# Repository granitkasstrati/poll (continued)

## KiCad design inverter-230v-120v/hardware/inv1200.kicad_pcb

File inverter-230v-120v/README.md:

# inv1200: 230 VAC → 120 VAC, 1200 W pure-sine converter

Non-isolated AC-DC-AC converter: inrush limiting, a UCC28180 CCM boost PFC to 400 V, a SiC full-bridge
inverter (unipolar SPWM, 40 kHz carrier, 80 kHz ripple), an LC filter, and an ESP32 controller.

| Path | What |
|---|---|
| `docs/DESIGN.md` | spec, calculations, protection, **what to verify**, bring-up procedure |
| `docs/PCB.md` | layout, clearance rules, regeneration steps |
| `hardware/inv1200.kicad_pro` | KiCad 7 project (schematic + PCB) |
| `hardware/fab/` | Gerbers + drill (zip), BOM CSV, pick-and-place, PDFs, renders |
| `hardware/gen/` | Python generators: `design.py` is the single source of truth for parts and nets |
| `firmware/inv1200/` | ESP-IDF ≥ 5.2 controller skeleton (**untested**) |

**Danger:** the whole board, including the ESP32 GND, is at mains potential; the 400 V bus holds ~94 J; and the 120 V
output is not isolated from the mains. Read `docs/DESIGN.md` §0/§7 before powering anything.

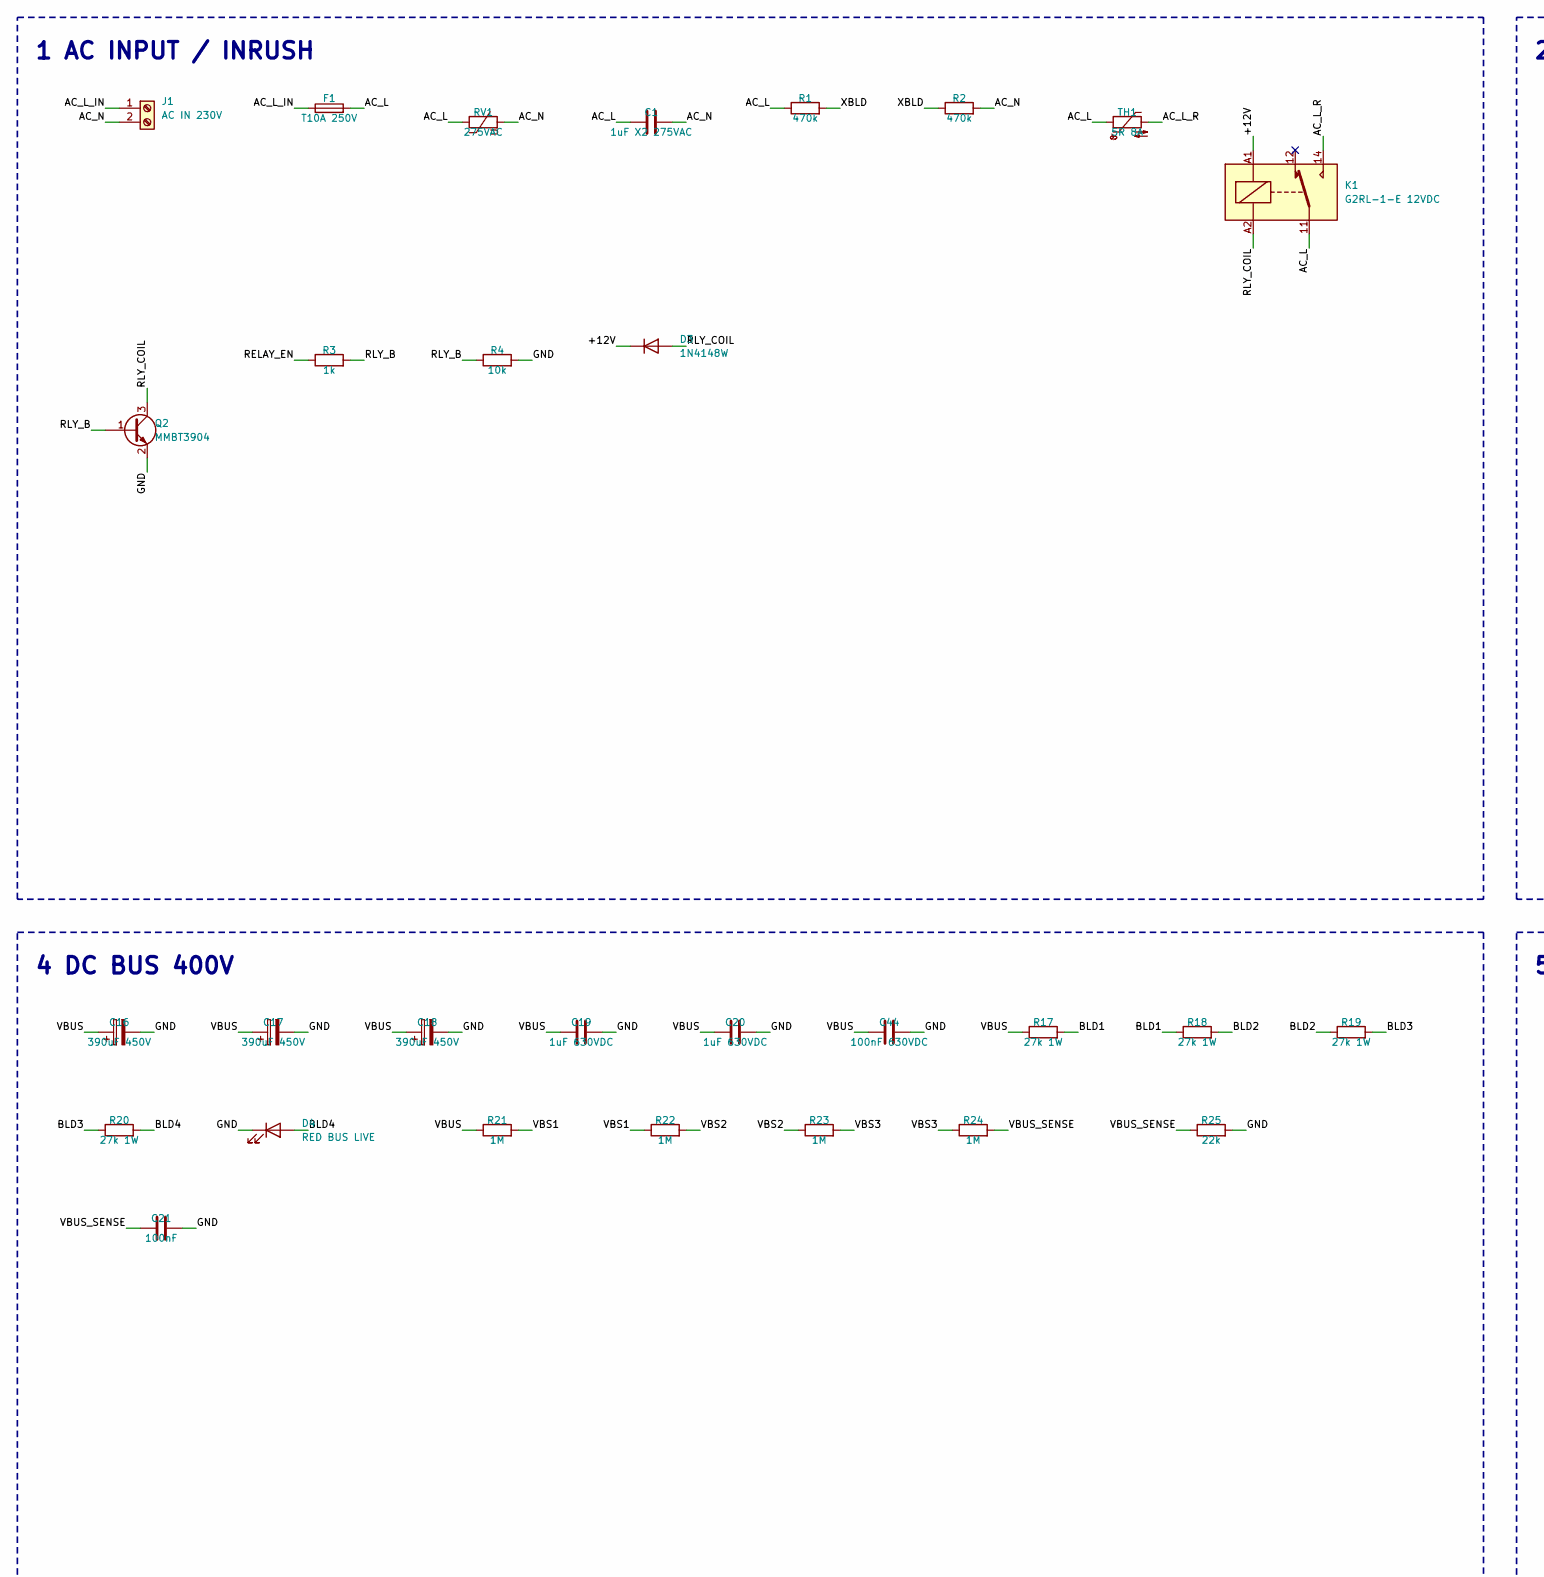
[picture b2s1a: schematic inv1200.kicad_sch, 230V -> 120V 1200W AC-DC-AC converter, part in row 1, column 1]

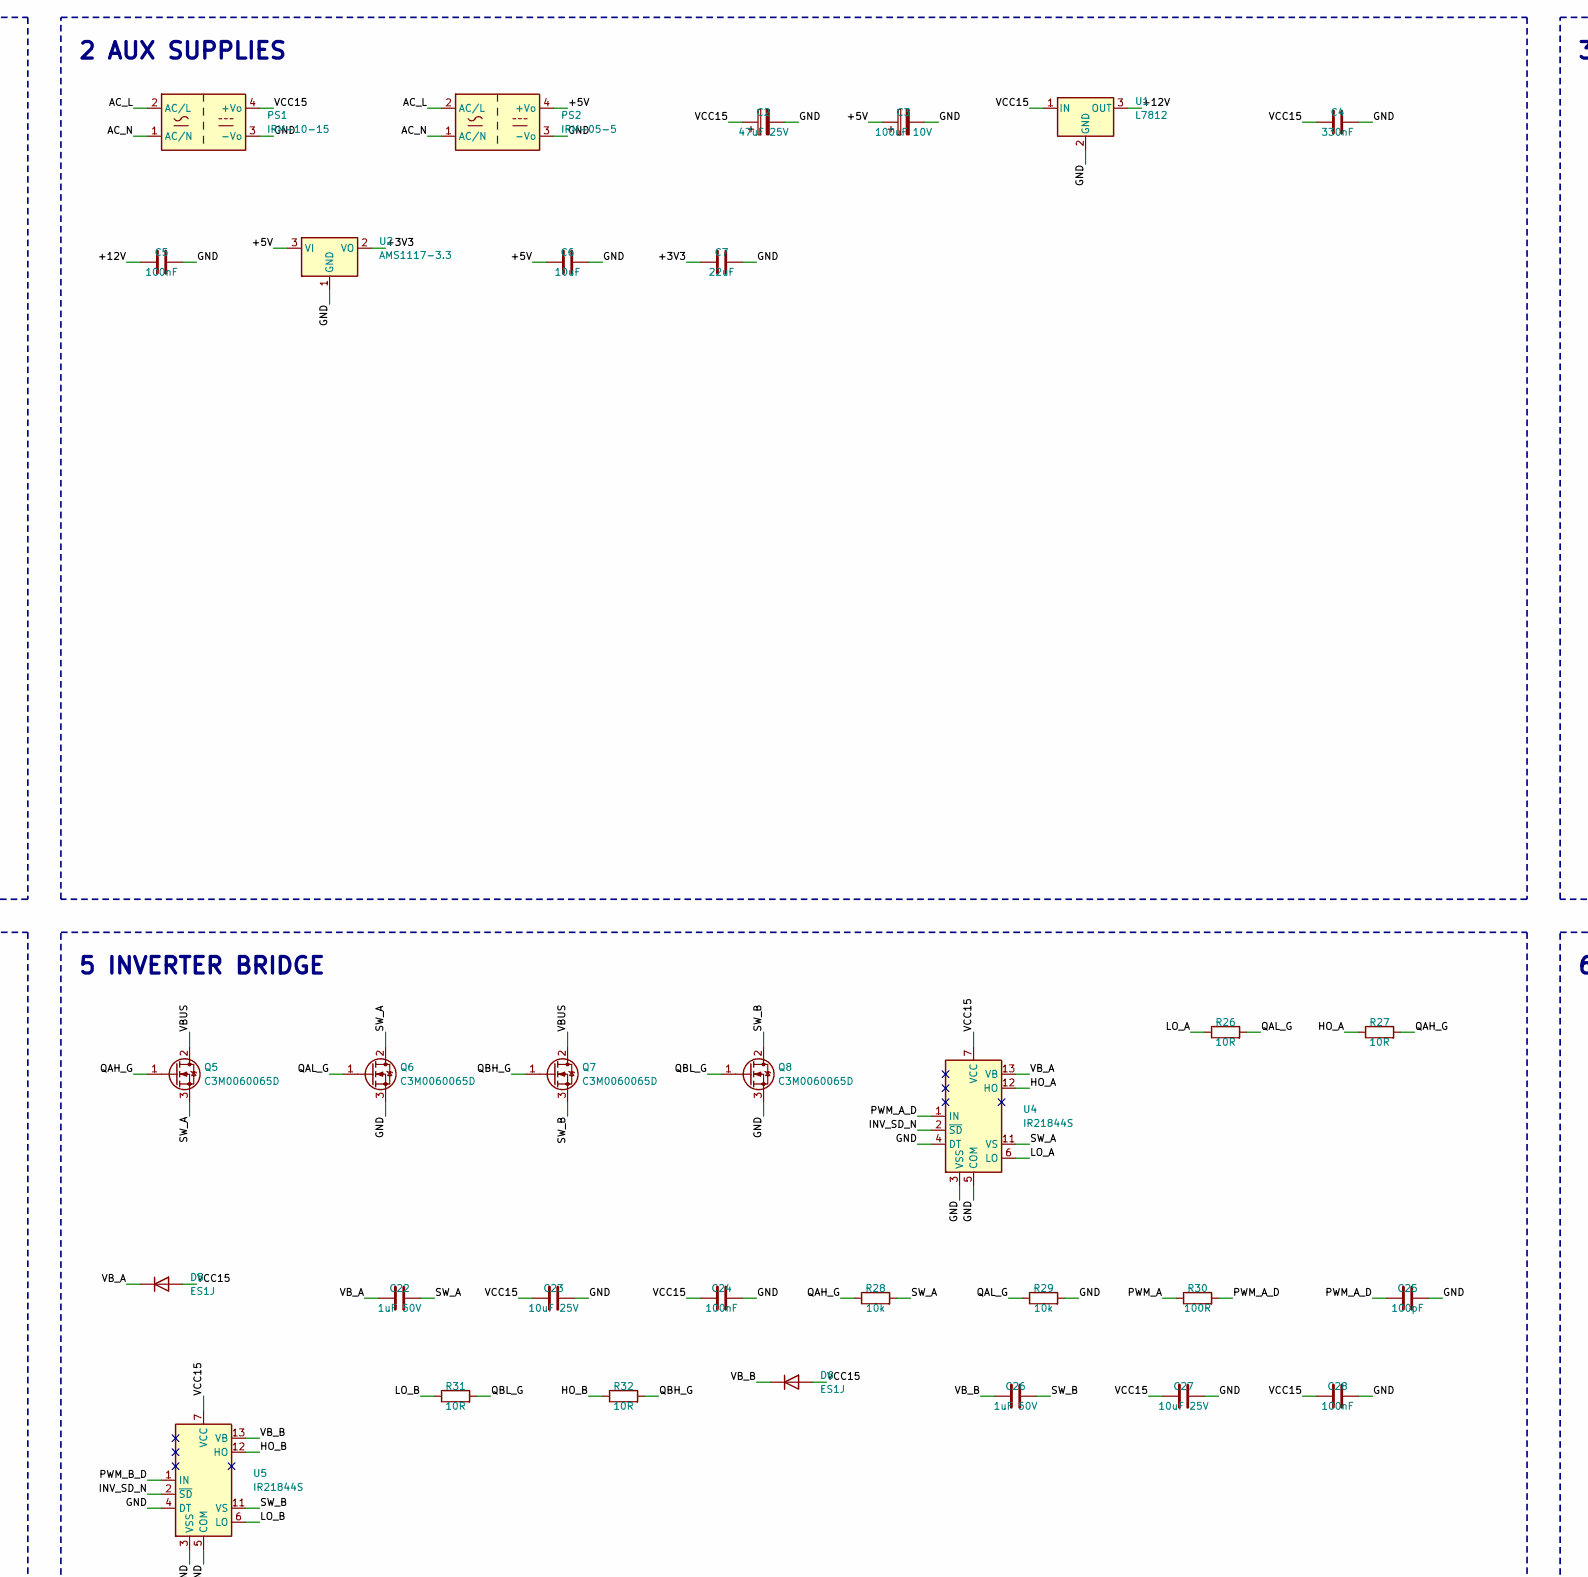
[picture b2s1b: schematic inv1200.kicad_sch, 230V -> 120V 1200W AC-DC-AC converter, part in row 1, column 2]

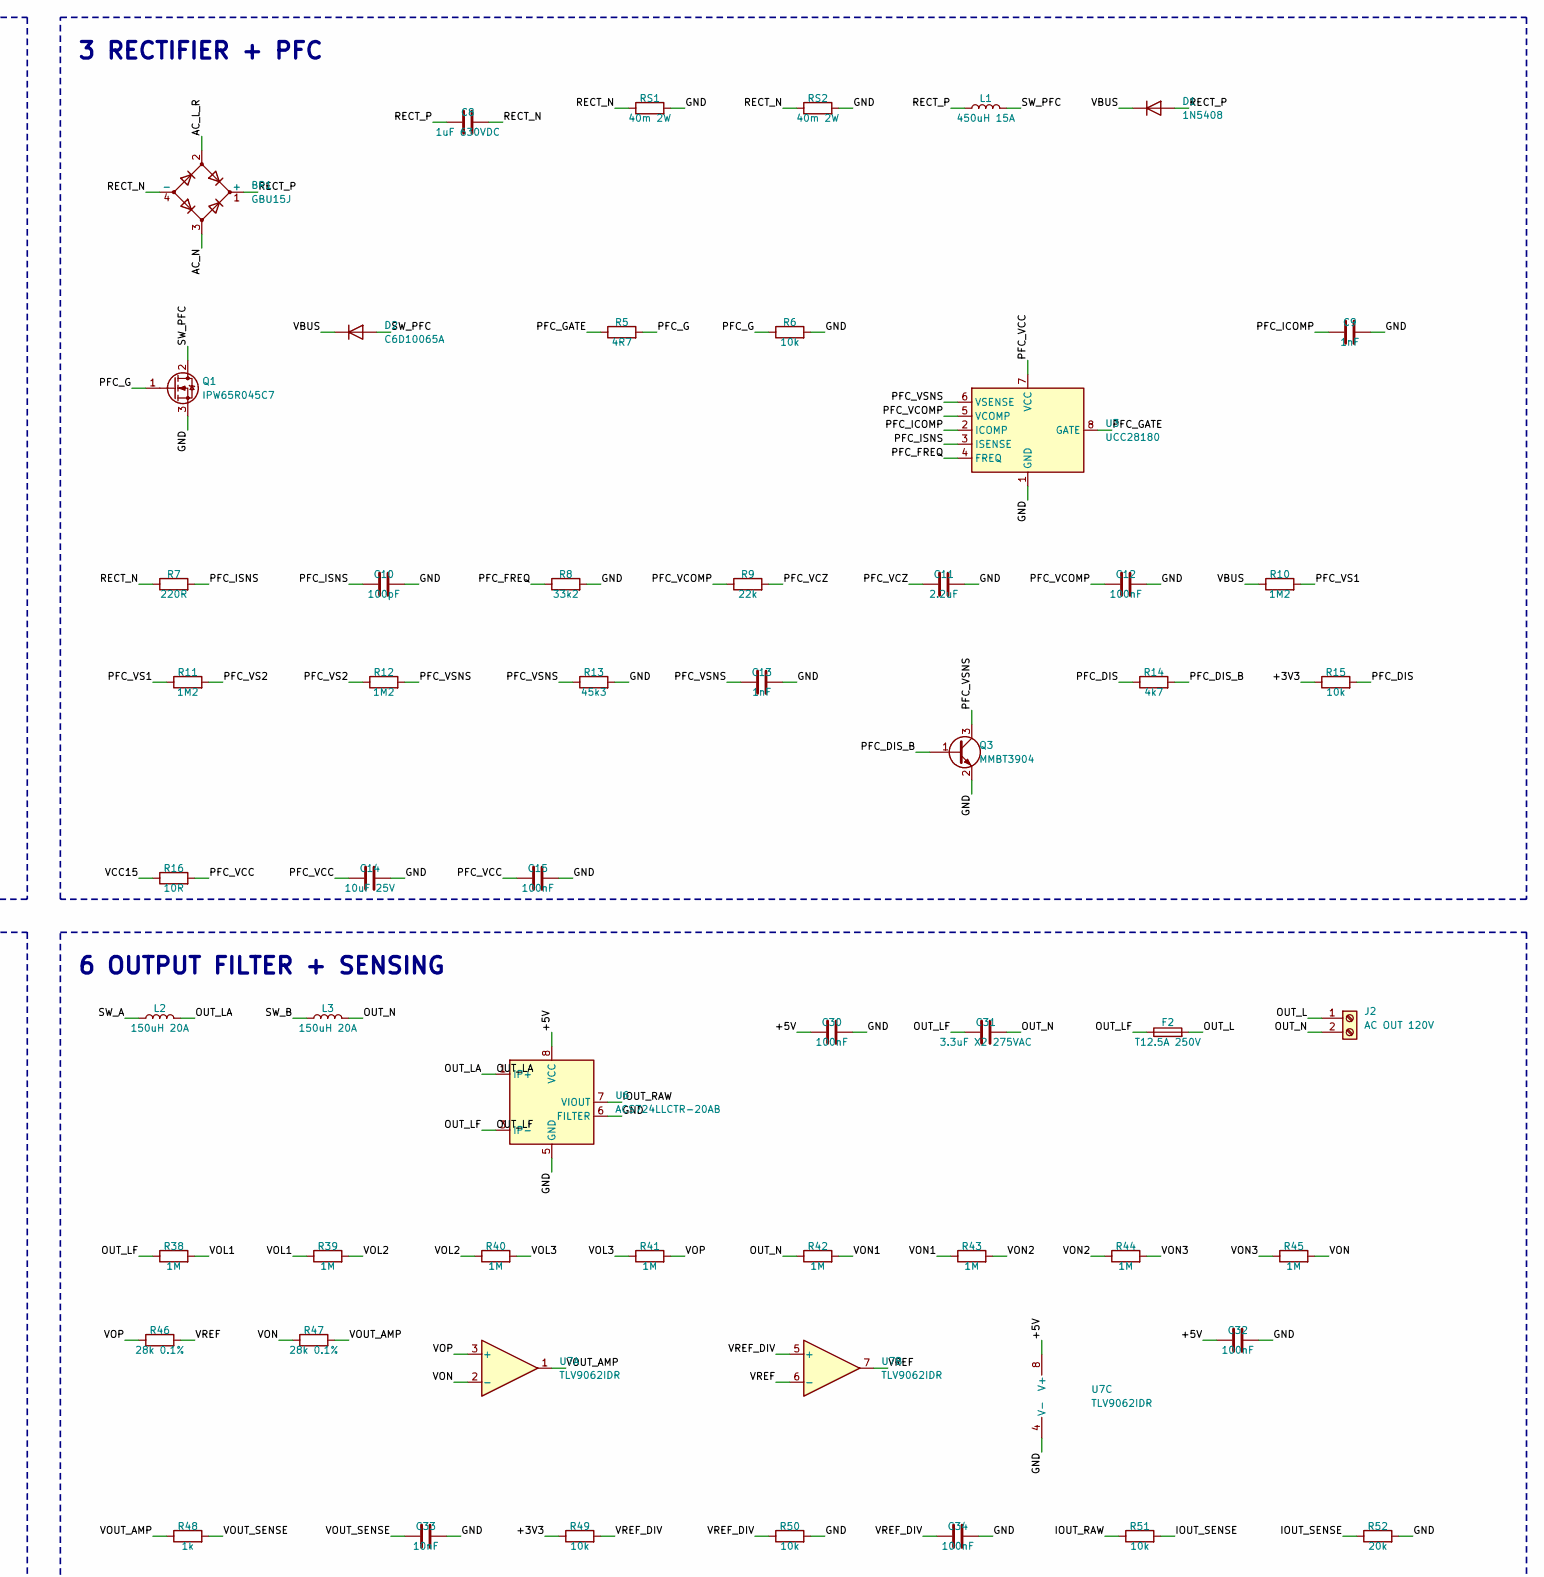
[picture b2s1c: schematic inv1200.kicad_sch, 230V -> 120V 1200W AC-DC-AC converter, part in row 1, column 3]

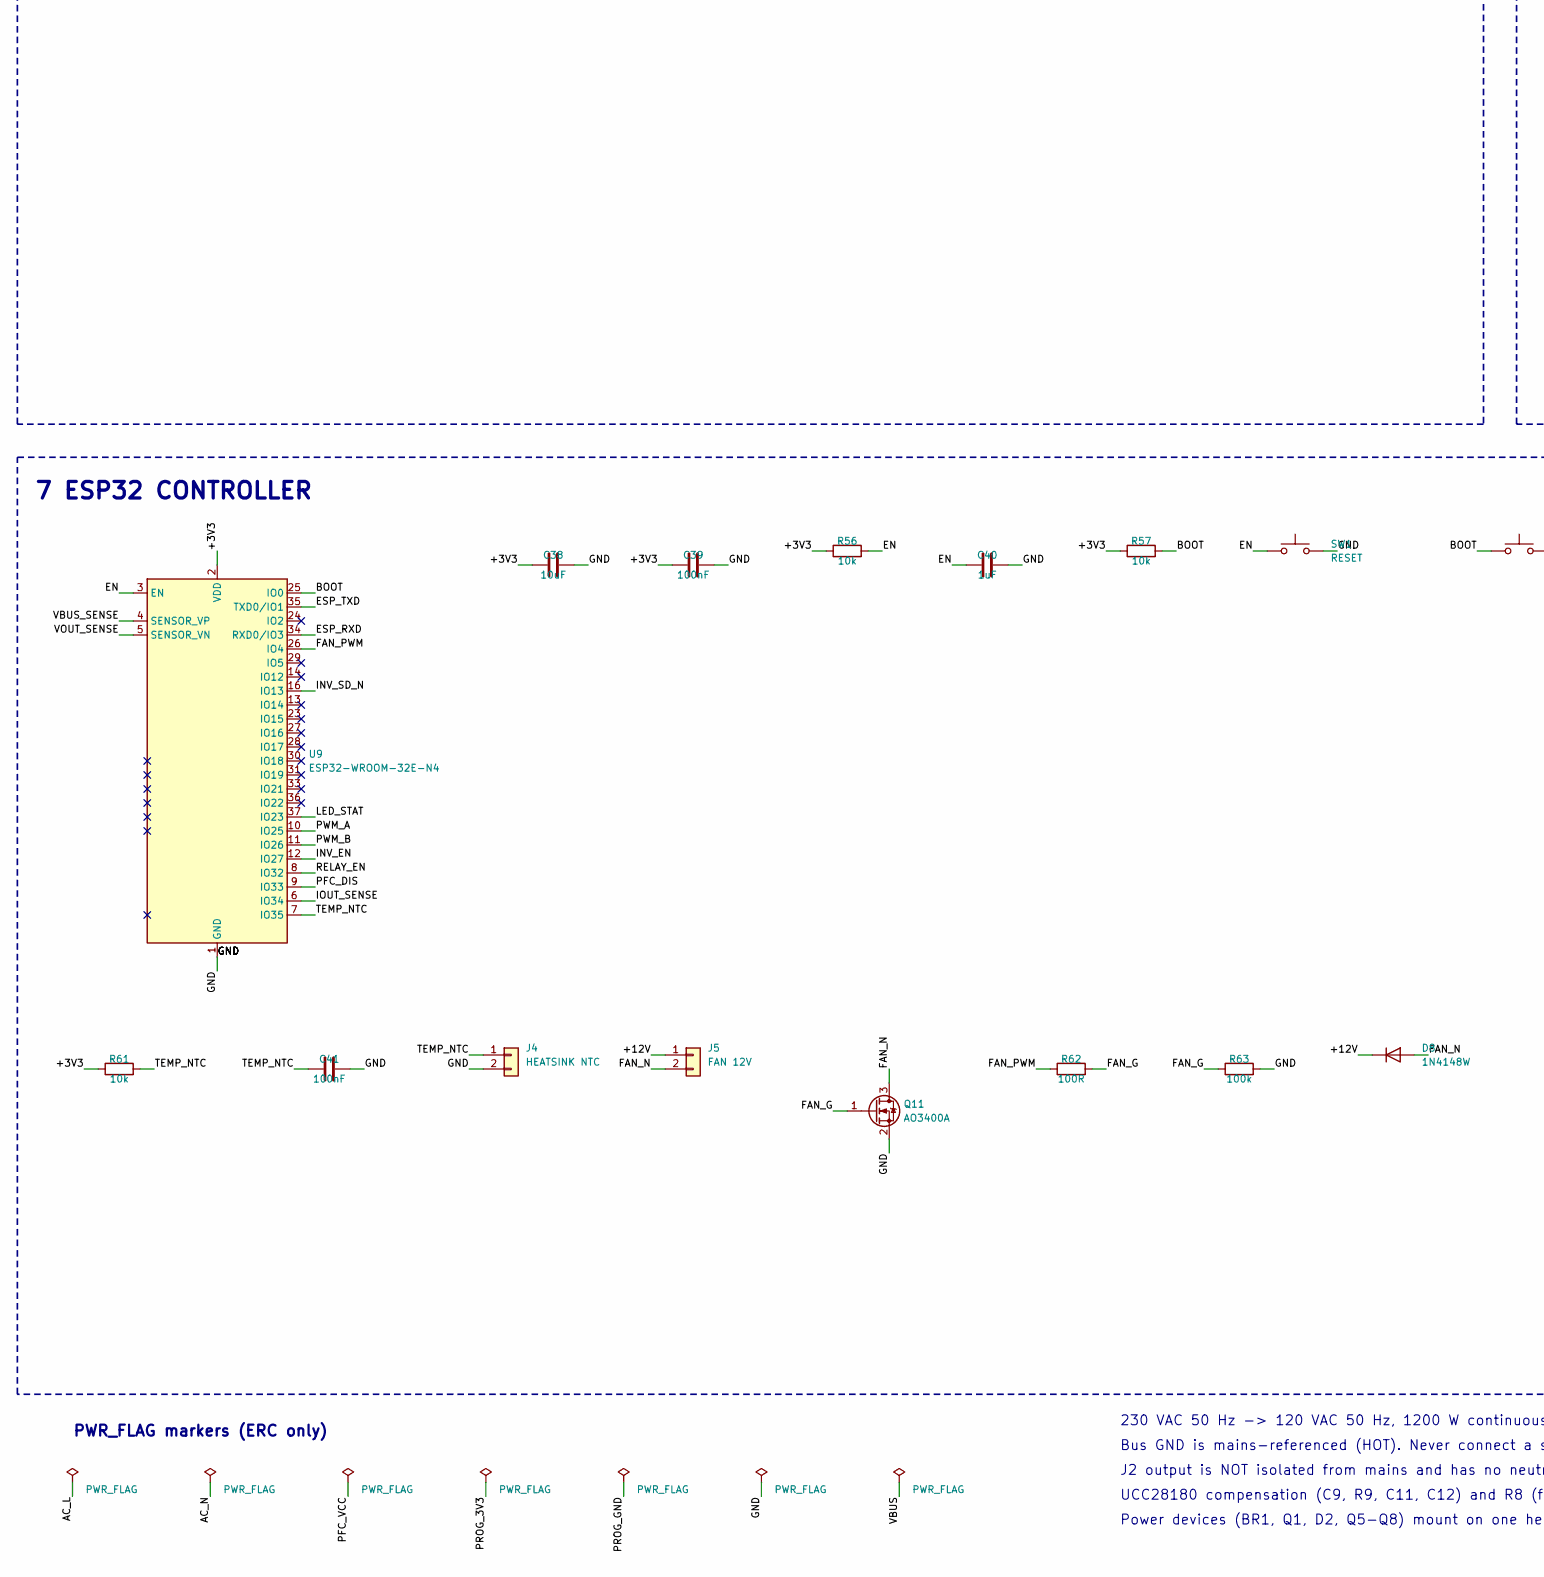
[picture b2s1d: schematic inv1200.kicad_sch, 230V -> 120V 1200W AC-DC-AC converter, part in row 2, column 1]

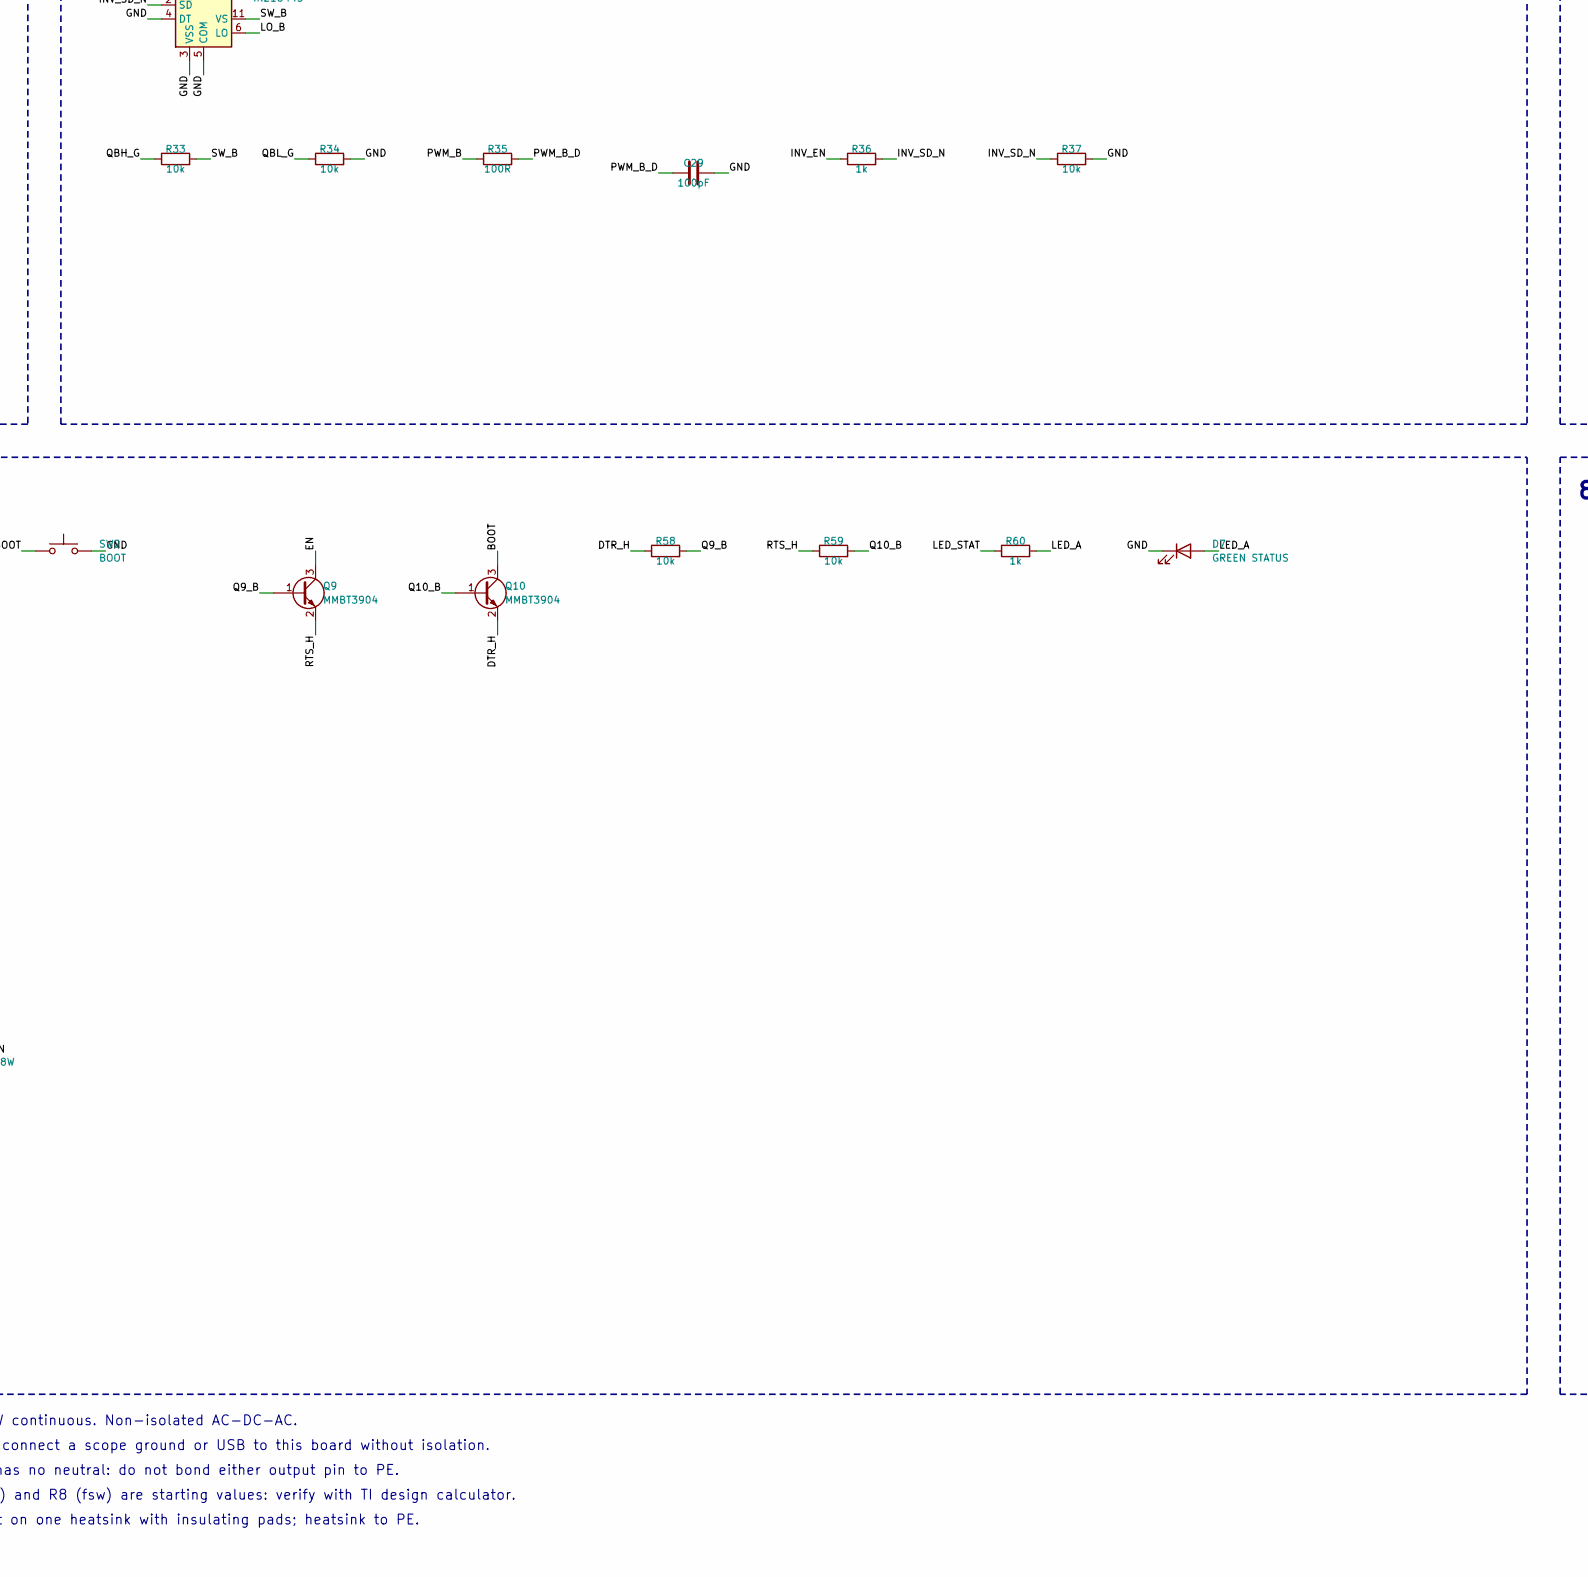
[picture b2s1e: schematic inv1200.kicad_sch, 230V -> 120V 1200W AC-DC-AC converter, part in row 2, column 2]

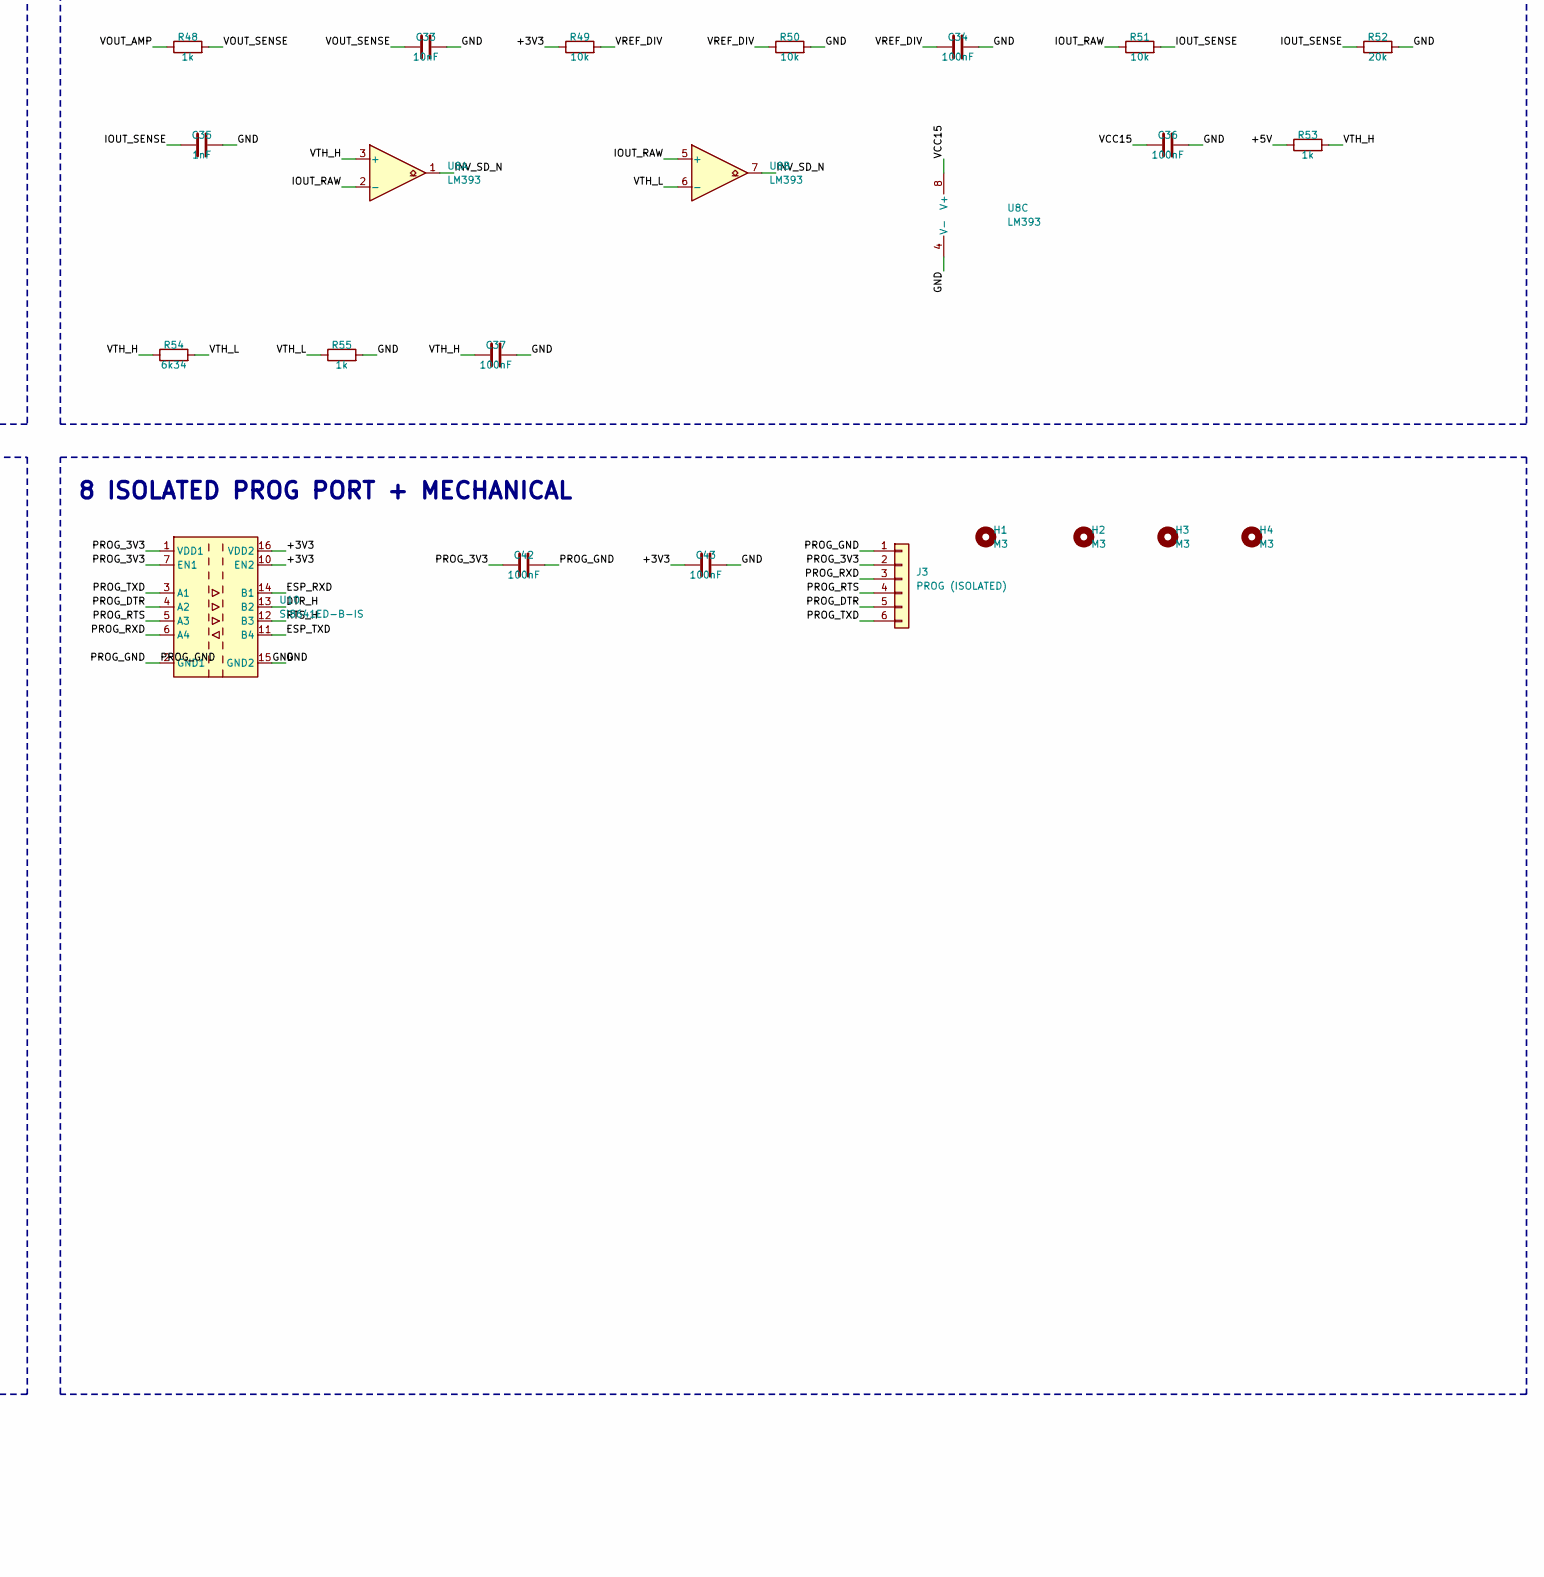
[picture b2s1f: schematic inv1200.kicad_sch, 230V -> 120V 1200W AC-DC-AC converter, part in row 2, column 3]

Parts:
BR1: GBU15J; Diode_Bridge_Vishay_GBU; MPN Vishay GBU15J or Diodes GBU1506 (15 A 6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
C1: 1uF X2 275VAC; C_Rect_L31.5mm_W13.0mm_P27.50mm_MKS4; MPN KEMET R46KR410000M1M / WIMA MKP X2
C2: 47uF 25V; CP_Radial_D6.3mm_P2.50mm
C3: 100uF 10V; CP_Radial_D6.3mm_P2.50mm
C4: 330nF; C_0805_2012Metric
C5, C12, C15, C21, C24, C28, C30, C32, C34, C36, C37, C39, C41, C42, C43: 100nF; C_0805_2012Metric
C6, C38: 10uF; C_0805_2012Metric
C7: 22uF; C_1206_3216Metric
C8: 1uF 630VDC; C_Rect_L26.5mm_W8.5mm_P22.50mm_MKS4; MPN WIMA MKP4 1uF 630VDC
C9, C13, C35: 1nF; C_0805_2012Metric
C10, C25, C29: 100pF; C_0805_2012Metric
C11: 2.2uF; C_0805_2012Metric
C14, C23, C27: 10uF 25V; C_1206_3216Metric
C16, C17, C18: 390uF 450V; CP_Radial_D35.0mm_P10.00mm_3pin_SnapIn; MPN Nichicon LGU2W391MELB / Rubycon 450MXK3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
C19, C20: 1uF 630VDC; C_Rect_L26.5mm_W8.5mm_P22.50mm_MKS4; MPN WIMA MKP4 1uF 630V
C22, C26: 1uF 50V; C_1206_3216Metric
C31: 3.3uF X2 275VAC; C_Rect_L31.5mm_W17.0mm_P27.50mm_MKS4; MPN KEMET R46 3.3uF X2 / WIMA MKP X2
C33: 10nF; C_0805_2012Metric
C40: 1uF; C_0805_2012Metric
C44: 100nF 630VDC; C_Rect_L18.0mm_W6.0mm_P15.00mm_FKS3_FKP3; MPN WIMA FKP3/MKP 100nF 630V
D1: 1N5408; D_DO-201AD_P15.24mm_Horizontal
D2: C6D10065A; TO-220-2_Vertical; MPN Wolfspeed C6D10065A SiC 650 V 10 A - on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
D3, D8: 1N4148W; D_SOD-123
D4: RED BUS LIVE; LED_0805_2012Metric
D5, D6: ES1J; D_SMA
D7: GREEN STATUS; LED_0805_2012Metric
F1: T10A 250V; Fuseholder_Cylinder-6.3x32mm_Schurter_0031-8002_Horizontal_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; MPN Schurter 0031.8002 holder + 6.3x32 T10A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
F2: T12.5A 250V; Fuseholder_Cylinder-6.3x32mm_Schurter_0031-8002_Horizontal_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; MPN Schurter 0031.8002 holder + 6.3x32 T12.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
H1, H2, H3, H4: M3; MountingHole_3.2mm_M3
J1: AC IN 230V; TerminalBlock_MetzConnect_Type067_RT01902HDWC_1x02_P10.00mm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; MPN Metz RT01902HDWC 10 mm pitch
J2: AC OUT 120V; TerminalBlock_MetzConnect_Type067_RT01902HDWC_1x02_P10.00mm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; MPN Metz RT01902HDWC 10 mm pitch
J3: PROG (ISOLATED); PinHeader_1x06_P2.54mm_Vertical
J4: HEATSINK NTC; JST_XH_B2B-XH-A_1x02_P2.50mm_Vertical; MPN 10k B3950 NTC glued to heatsink, insula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
J5: FAN 12V; JST_XH_B2B-XH-A_1x02_P2.50mm_Vertical
K1: G2RL-1-E 12VDC; Relay_SPDT_Omron_G2RL-1-E; MPN Omron G2RL-1-E DC12 (16 A)
L1: 450uH 15A; L_Toroid_Vertical_L67.6mm_W36.1mm_P31.80mm_Vishay_TJ9; MPN 2x Magnetics 0077439A7 Kool Mu 60u stac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
L2, L3: 150uH 20A; L_Toroid_Vertical_L67.6mm_W36.1mm_P31.80mm_Vishay_TJ9; MPN Kool Mu 0077439A7 ~45 T 1.8 mm (Isat >=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
PS1: IRM-10-15; Converter_ACDC_MeanWell_IRM-10-xx_THT; MPN Mean Well IRM-10-15
PS2: IRM-05-5; Converter_ACDC_MeanWell_IRM-05-xx_THT; MPN Mean Well IRM-05-5
Q1: IPW65R045C7; TO-247-3_Vertical; MPN Infineon IPW65R045C7 - on heatsink
Q2, Q3, Q9, Q10: MMBT3904; SOT-23
Q5, Q6, Q7, Q8: C3M0060065D; TO-247-3_Vertical; MPN Wolfspeed C3M0060065D SiC - on heatsink
Q11: AO3400A; SOT-23
R1, R2: 470k; R_2512_6332Metric
R3, R36, R48, R53, R55, R60: 1k; R_0805_2012Metric
R4, R6, R15, R28, R29, R33, R34, R37, R49, R50, R51, R56, R57, R58, R59, R61: 10k; R_0805_2012Metric
R5: 4R7; R_0805_2012Metric
R7: 220R; R_0805_2012Metric
R8: 33k2; R_0805_2012Metric
R9, R25: 22k; R_0805_2012Metric
R10: 1M2; R_2512_6332Metric
R11, R12: 1M2; R_1206_3216Metric
R13: 45k3; R_0805_2012Metric
R14: 4k7; R_0805_2012Metric
R16, R26, R27, R31, R32: 10R; R_0805_2012Metric
R17, R18, R19, R20: 27k 1W; R_2512_6332Metric
R21, R38, R42: 1M; R_2512_6332Metric
R22, R23, R24, R39, R40, R41, R43, R44, R45: 1M; R_1206_3216Metric
R30, R35, R62: 100R; R_0805_2012Metric
R46, R47: 28k 0.1%; R_0805_2012Metric
R52: 20k; R_0805_2012Metric
R54: 6k34; R_0805_2012Metric
R63: 100k; R_0805_2012Metric
RS1: 40m 2W; R_2512_6332Metric; MPN Vishay WSL2512R0400 (or Bourns CRA2512)
RS2: 40m 2W; R_2512_6332Metric; MPN Vishay WSL2512R0400
RV1: 275VAC; RV_Disc_D15.5mm_W5.9mm_P7.5mm; MPN TDK S14K275
SW1: RESET; SW_SPST_TL3342
SW2: BOOT; SW_SPST_TL3342
TH1: 5R 8A; RV_Disc_D15.5mm_W5.9mm_P7.5mm; MPN TDK B57237S0509M000 (S237, 5 ohm, 8 A)
U1: L7812; TO-220-3_Vertical; MPN ST L7812CV
U2: AMS1117-3.3; SOT-223-3_TabPin2
U3: UCC28180; SOIC-8_3.9x4.9mm_P1.27mm; MPN TI UCC28180DR
U4, U5: IR21844S; SOIC-14_3.9x8.7mm_P1.27mm; MPN Infineon IR21844STRPBF
U6: ACS724LLCTR-20AB; SOIC-8_3.9x4.9mm_P1.27mm; MPN Allegro ACS724LLCTR-20AB-T
U7: TLV9062IDR; SOIC-8_3.9x4.9mm_P1.27mm; MPN TI TLV9062IDR
U8: LM393; SOIC-8_3.9x4.9mm_P1.27mm; MPN TI LM393DR
U9: ESP32-WROOM-32E-N4; ESP32-WROOM-32D; MPN Espressif ESP32-WROOM-32E-N4
U10: Si8641ED-B-IS; SOIC-16W_7.5x10.3mm_P1.27mm; MPN Skyworks Si8641ED-B-IS (5 kVrms, defaul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

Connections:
+3V3: C7.1, C38.1, C39.1, C43.1, R15.1, R49.1, R56.1, R57.1, R61.1, U2.2 (VO), U9.2 (VDD), U10.10 (EN2), U10.16 (VDD2)
+5V: C3.1, C6.1, C30.1, C32.1, PS2.4 (+Vo), R53.1, U2.3 (VI), U6.8 (VCC), U7.8 (V+)
+12V: C5.1, D3.1 (K), D8.1 (K), J5.1, K1.A1, U1.3 (OUT)
AC_L: C1.1, F1.2, K1.11, PS1.2 (AC/L), PS2.2 (AC/L), R1.1, RV1.1, TH1.1
AC_L_IN: F1.1, J1.1
AC_L_R: BR1.2, K1.14, TH1.2
AC_N: BR1.3, C1.2, J1.2, PS1.1 (AC/N), PS2.1 (AC/N), R2.2, RV1.2
BLD1: R17.2, R18.1
BLD2: R18.2, R19.1
BLD3: R19.2, R20.1
BLD4: D4.2 (A), R20.2
BOOT: Q10.3 (C), R57.2, SW2.1, U9.25 (IO0)
DTR_H: Q10.2 (E), R58.1, U10.13 (B2)
EN: C40.1, Q9.3 (C), R56.2, SW1.1, U9.3 (EN)
ESP_RXD: U9.34 (RXD0/IO3), U10.14 (B1)
ESP_TXD: U9.35 (TXD0/IO1), U10.11 (B4)
FAN_G: Q11.1 (G), R62.2, R63.1
FAN_N: D8.2 (A), J5.2, Q11.3 (D)
FAN_PWM: R62.1, U9.26 (IO4)
GND: C2.2, C3.2, C4.2, C5.2, C6.2, C7.2, C9.2, C10.2, C11.2, C12.2, C13.2, C14.2, C15.2, C16.2, C17.2, C18.2, C19.2, C20.2, C21.2, C23.2, C24.2, C25.2, C27.2, C28.2, C29.2, C30.2, C32.2, C33.2, C34.2, C35.2, C36.2, C37.2, C38.2, C39.2, C40.2, C41.2, C43.2, C44.2, D4.1 (K), D7.1 (K), J4.2, PS1.3 (-Vo), PS2.3 (-Vo), Q1.3 (S), Q2.2 (E), Q3.2 (E), Q6.3 (S), Q8.3 (S), Q11.2 (S), R4.2, R6.2, R8.2, R13.2, R25.2, R29.2, R34.2, R37.2, R50.2, R52.2, R55.2, R63.2, RS1.2, RS2.2, SW1.2, SW2.2, U1.2 (GND), U2.1 (GND), U3.1 (GND), U4.3 (VSS), U4.4 (DT), U4.5 (COM), U5.3 (VSS), U5.4 (DT), U5.5 (COM), U6.5 (GND), U6.6 (FILTER), U7.4 (V-), U8.4 (V-), U9.1 (GND), U9.15 (GND), U9.38 (GND), U9.39 (GND), U10.9 (GND2), U10.15 (GND2)
HO_A: R27.1, U4.12 (HO)
HO_B: R32.1, U5.12 (HO)
INV_EN: R36.1, U9.12 (IO27)
INV_SD_N: R36.2, R37.1, U4.2 (~SD), U5.2 (~SD), U8.1, U8.7, U9.16 (IO13)
IOUT_RAW: R51.1, U6.7 (VIOUT), U8.2 (-), U8.5 (+)
IOUT_SENSE: C35.1, R51.2, R52.1, U9.6 (IO34)
LED_A: D7.2 (A), R60.2
LED_STAT: R60.1, U9.37 (IO23)
LO_A: R26.1, U4.6 (LO)
LO_B: R31.1, U5.6 (LO)
OUT_L: F2.2, J2.1
OUT_LA: L2.2, U6.1 (IP+), U6.2 (IP+)
OUT_LF: C31.1, F2.1, R38.1, U6.3 (IP-), U6.4 (IP-)
OUT_N: C31.2, J2.2, L3.2, R42.1
PFC_DIS: R14.1, R15.2, U9.9 (IO33)
PFC_DIS_B: Q3.1 (B), R14.2
PFC_FREQ: R8.1, U3.4 (FREQ)
PFC_G: Q1.1 (G), R5.2, R6.1
PFC_GATE: R5.1, U3.8 (GATE)
PFC_ICOMP: C9.1, U3.2 (ICOMP)
PFC_ISNS: C10.1, R7.2, U3.3 (ISENSE)
PFC_VCC: C14.1, C15.1, R16.2, U3.7 (VCC)
PFC_VCOMP: C12.1, R9.1, U3.5 (VCOMP)
PFC_VCZ: C11.1, R9.2
PFC_VS1: R10.2, R11.1
PFC_VS2: R11.2, R12.1
PFC_VSNS: C13.1, Q3.3 (C), R12.2, R13.1, U3.6 (VSENSE)
PROG_3V3: C42.1, J3.2, U10.1 (VDD1), U10.7 (EN1)
PROG_DTR: J3.5, U10.4 (A2)
PROG_GND: C42.2, J3.1, U10.2 (GND1), U10.8 (GND1)
PROG_RTS: J3.4, U10.5 (A3)
PROG_RXD: J3.3, U10.6 (A4)
PROG_TXD: J3.6, U10.3 (A1)
PWM_A: R30.1, U9.10 (IO25)
PWM_A_D: C25.1, R30.2, U4.1 (IN)
PWM_B: R35.1, U9.11 (IO26)
PWM_B_D: C29.1, R35.2, U5.1 (IN)
Q9_B: Q9.1 (B), R58.2
Q10_B: Q10.1 (B), R59.2
QAH_G: Q5.1 (G), R27.2, R28.1
QAL_G: Q6.1 (G), R26.2, R29.1
QBH_G: Q7.1 (G), R32.2, R33.1
QBL_G: Q8.1 (G), R31.2, R34.1
RECT_N: BR1.4 (-), C8.2, R7.1, RS1.1, RS2.1
RECT_P: BR1.1 (+), C8.1, D1.2 (A), L1.1
RELAY_EN: R3.1, U9.8 (IO32)
RLY_B: Q2.1 (B), R3.2, R4.1
RLY_COIL: D3.2 (A), K1.A2, Q2.3 (C)
RTS_H: Q9.2 (E), R59.1, U10.12 (B3)
SW_A: C22.2, L2.1, Q5.3 (S), Q6.2 (D), R28.2, U4.11 (VS)
SW_B: C26.2, L3.1, Q7.3 (S), Q8.2 (D), R33.2, U5.11 (VS)
SW_PFC: D2.2 (A), L1.2, Q1.2 (D)
TEMP_NTC: C41.1, J4.1, R61.2, U9.7 (IO35)
VBS1: R21.2, R22.1
VBS2: R22.2, R23.1
VBS3: R23.2, R24.1
VBUS: C16.1, C17.1, C18.1, C19.1, C20.1, C44.1, D1.1 (K), D2.1 (K), Q5.2 (D), Q7.2 (D), R10.1, R17.1, R21.1
VBUS_SENSE: C21.1, R24.2, R25.1, U9.4 (SENSOR_VP)
VB_A: C22.1, D5.1 (K), U4.13 (VB)
VB_B: C26.1, D6.1 (K), U5.13 (VB)
VCC15: C2.1, C4.1, C23.1, C24.1, C27.1, C28.1, C36.1, D5.2 (A), D6.2 (A), PS1.4 (+Vo), R16.1, U1.1 (IN), U4.7 (VCC), U5.7 (VCC), U8.8 (V+)
VOL1: R38.2, R39.1
VOL2: R39.2, R40.1
VOL3: R40.2, R41.1
VON: R45.2, R47.1, U7.2 (-)
VON1: R42.2, R43.1
VON2: R43.2, R44.1
VON3: R44.2, R45.1
VOP: R41.2, R46.1, U7.3 (+)
VOUT_AMP: R47.2, R48.1, U7.1
VOUT_SENSE: C33.1, R48.2, U9.5 (SENSOR_VN)
VREF: R46.2, U7.6 (-), U7.7
VREF_DIV: C34.1, R49.2, R50.1, U7.5 (+)
VTH_H: C37.1, R53.2, R54.1, U8.3 (+)
VTH_L: R54.2, R55.1, U8.6 (-)
XBLD: R1.2, R2.1

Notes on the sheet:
1 AC INPUT / INRUSH
2 AUX SUPPLIES
3 RECTIFIER + PFC
4 DC BUS 400V
5 INVERTER BRIDGE
6 OUTPUT FILTER + SENSING
7 ESP32 CONTROLLER
8 ISOLATED PROG PORT + MECHANICAL
PWR_FLAG markers (ERC only)
230 VAC 50 Hz -> 120 VAC 50 Hz, 1200 W continuous. Non-isolated AC-DC-AC.
Bus GND is mains-referenced (HOT). Never connect a scope ground or USB to this board without isolation.
J2 output is NOT isolated from mains and has no neutral: do not bond either output pin to PE.
UCC28180 compensation (C9, R9, C11, C12) and R8 (fsw) are starting values: verify with TI design calculator.
Power devices (BR1, Q1, D2, Q5-Q8) mount on one heatsink with insulating pads; heatsink to PE.
